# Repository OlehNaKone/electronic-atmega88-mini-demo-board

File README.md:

# electronic-atmega88-mini-demo-board

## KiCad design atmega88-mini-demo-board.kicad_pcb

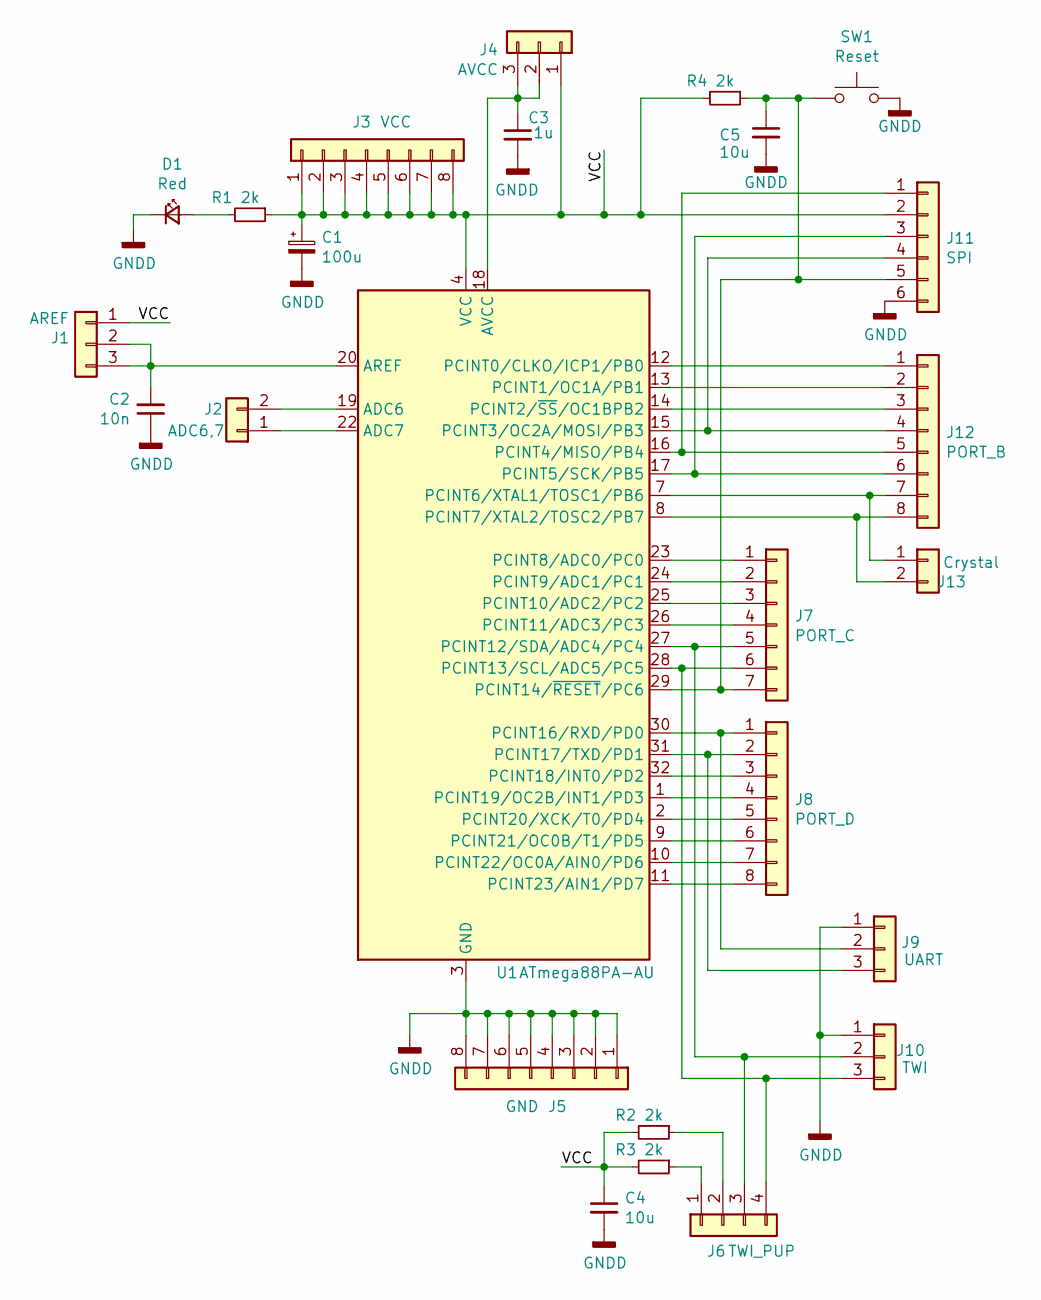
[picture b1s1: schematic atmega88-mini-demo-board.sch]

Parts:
C1: 100u; CP_Radial_D5.0mm_P2.50mm
C2: 10n; C_1206_3216Metric_Pad1.42x1.75mm_HandSolder
C3: 1u; C_1206_3216Metric_Pad1.42x1.75mm_HandSolder
C4, C5: 10u; C_1210_3225Metric_Pad1.42x2.65mm_HandSolder
D1: Red; LED_0805_2012Metric_Pad1.15x1.40mm_HandSolder
J1: AREF; PinHeader_1x03_P2.54mm_Vertical
J2: ADC6,7; PinHeader_1x02_P2.54mm_Vertical
J3: VCC; PinHeader_2x04_P2.54mm_Vertical
J4: AVCC; PinHeader_1x03_P2.54mm_Vertical
J5: GND; PinHeader_2x04_P2.54mm_Vertical
J6: TWI_PUP; PinHeader_2x02_P2.54mm_Vertical
J7: PORT_C; PinHeader_1x07_P2.54mm_Vertical
J8: PORT_D; PinHeader_1x08_P2.54mm_Vertical
J9: UART; PinHeader_1x03_P2.54mm_Vertical
J10: TWI; PinHeader_1x03_P2.54mm_Vertical
J11: SPI; PinHeader_2x03_P2.54mm_Vertical
J12: PORT_B; PinHeader_1x08_P2.54mm_Vertical
J13: Crystal; PinSocket_1x02_P2.54mm_Vertical
R1, R2, R3, R4: 2k; R_0805_2012Metric_Pad1.15x1.40mm_HandSolder
SW1: Reset; SW_SPST_FSMSM
U1: ATmega88PA-AU; TQFP-32_7x7mm_P0.8mm

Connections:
/VCC: C1.1, C4.1, J1.1, J3.1, J3.2, J3.3, J3.4, J3.5, J3.6, J3.7, J3.8, J4.1, J11.2, R1.1, R2.2, R3.2, R4.2, U1.4 (VCC), U1.6 (VCC)
GNDD: C1.2, C2.1, C3.2, C4.2, C5.2, D1.1 (K), J5.1, J5.2, J5.3, J5.4, J5.5, J5.6, J5.7, J5.8, J9.1, J10.1, J11.6, SW1.2, U1.3 (GND), U1.5 (GND), U1.21 (GND)
unnamed: C2.2, J1.2, J1.3, U1.20 (AREF)
unnamed: C3.1, J4.2, J4.3, U1.18 (AVCC)
unnamed: C5.1, J7.7, J11.5, R4.1, SW1.1, U1.29 (PCINT14/~RESET~/PC6)
unnamed: D1.2 (A), R1.2
unnamed: J2.1, U1.22 (ADC7)
unnamed: J2.2, U1.19 (ADC6)
unnamed: J6.1, R3.1
unnamed: J6.2, R2.1
unnamed: J7.1, U1.23 (PCINT8/ADC0/PC0)
unnamed: J7.2, U1.24 (PCINT9/ADC1/PC1)
unnamed: J7.3, U1.25 (PCINT10/ADC2/PC2)
unnamed: J7.4, U1.26 (PCINT11/ADC3/PC3)
unnamed: J8.1, J9.2, U1.30 (PCINT16/RXD/PD0)
unnamed: J8.2, J9.3, U1.31 (PCINT17/TXD/PD1)
unnamed: J8.3, U1.32 (PCINT18/INT0/PD2)
unnamed: J8.4, U1.1 (PCINT19/OC2B/INT1/PD3)
unnamed: J8.5, U1.2 (PCINT20/XCK/T0/PD4)
unnamed: J8.6, U1.9 (PCINT21/OC0B/T1/PD5)
unnamed: J8.7, U1.10 (PCINT22/OC0A/AIN0/PD6)
unnamed: J8.8, U1.11 (PCINT23/AIN1/PD7)
unnamed: J6.3, J7.5, J10.2, U1.27 (PCINT12/SDA/ADC4/PC4)
unnamed: J6.4, J7.6, J10.3, U1.28 (PCINT13/SCL/ADC5/PC5)
unnamed: J11.1, J12.5, U1.16 (PCINT4/MISO/PB4)
unnamed: J11.3, J12.6, U1.17 (PCINT5/SCK/PB5)
unnamed: J11.4, J12.4, U1.15 (PCINT3/OC2A/MOSI/PB3)
unnamed: J12.1, U1.12 (PCINT0/CLKO/ICP1/PB0)
unnamed: J12.2, U1.13 (PCINT1/OC1A/PB1)
unnamed: J12.3, U1.14 (PCINT2/~SS~/OC1BPB2)
unnamed: J12.7, J13.1, U1.7 (PCINT6/XTAL1/TOSC1/PB6)
unnamed: J12.8, J13.2, U1.8 (PCINT7/XTAL2/TOSC2/PB7)

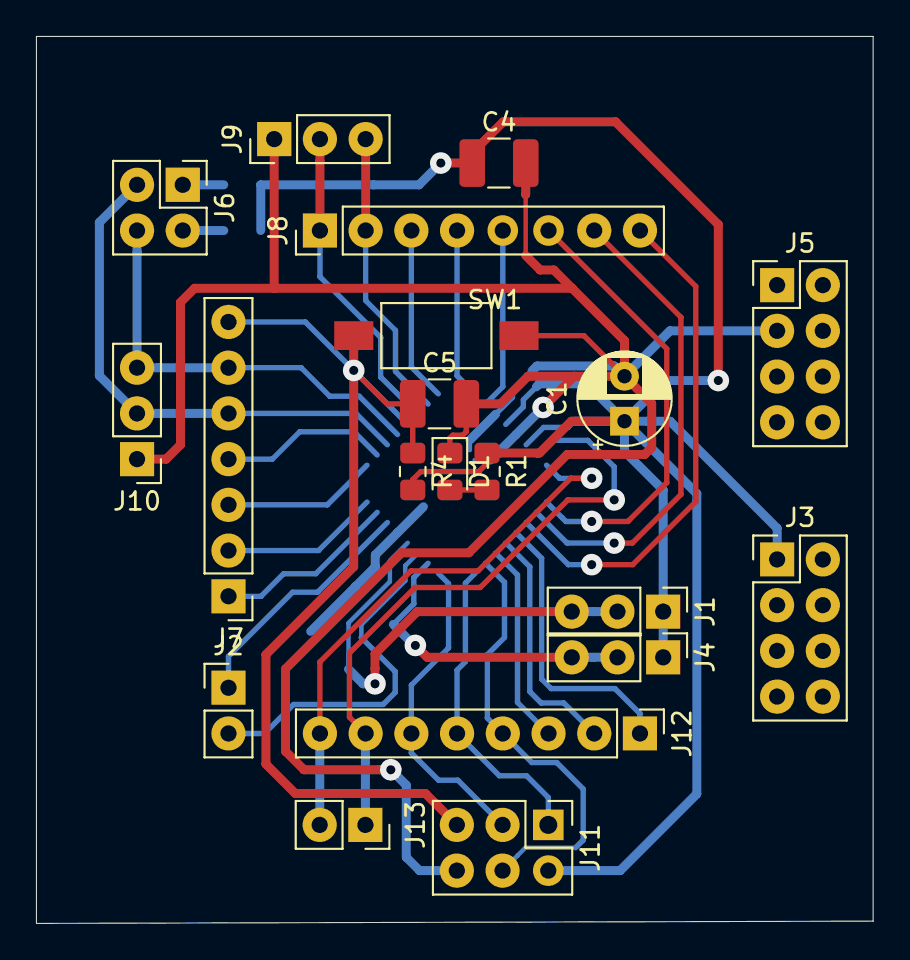
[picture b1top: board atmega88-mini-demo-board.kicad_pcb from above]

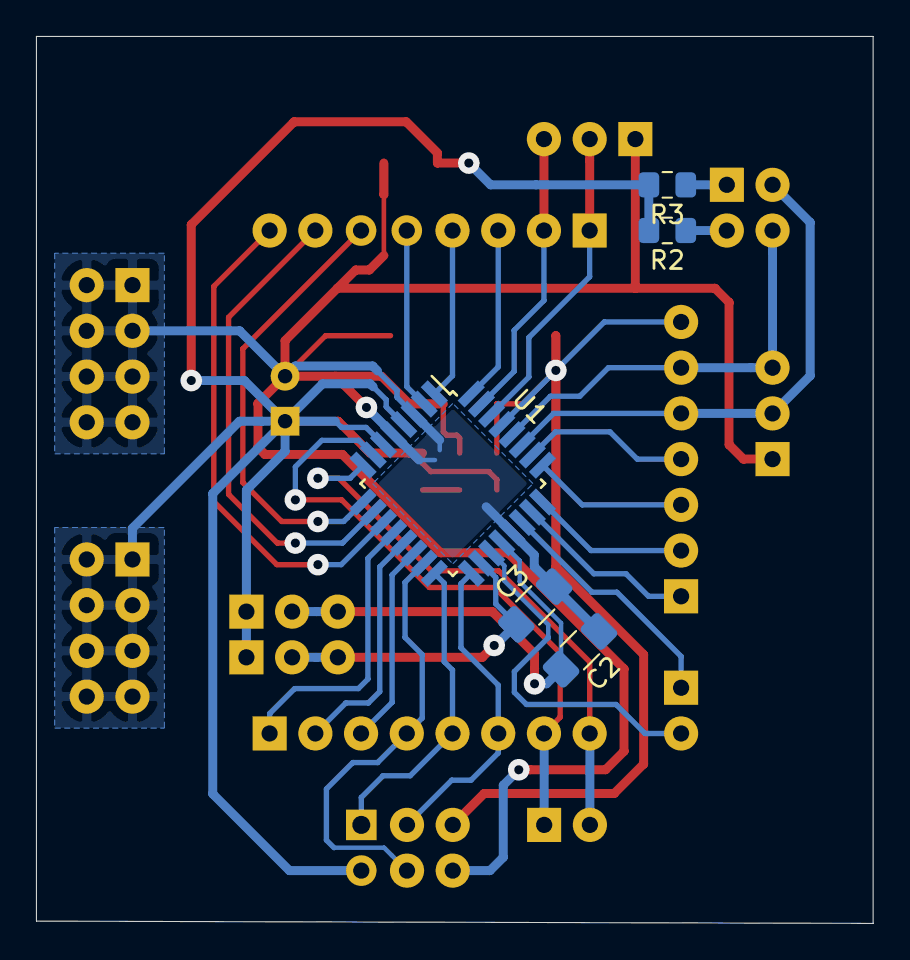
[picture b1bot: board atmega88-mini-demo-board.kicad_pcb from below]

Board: 2 copper layers, 46.5 x 49.3 mm, 25 parts (5 on the bottom side), 32 nets.

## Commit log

2022-04-05 init
